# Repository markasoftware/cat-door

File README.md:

# cat-door

KiCAD files and ATtiny84 firmware for my [cat door](https://markasoftware.com/cat-door).

The state machine diagram is old and incorrect. The unit tests in `test.lisp` do
not work, partially because they are written rong, and partially because simavr
seems to have bugs related to inputs with pull-up resistors.

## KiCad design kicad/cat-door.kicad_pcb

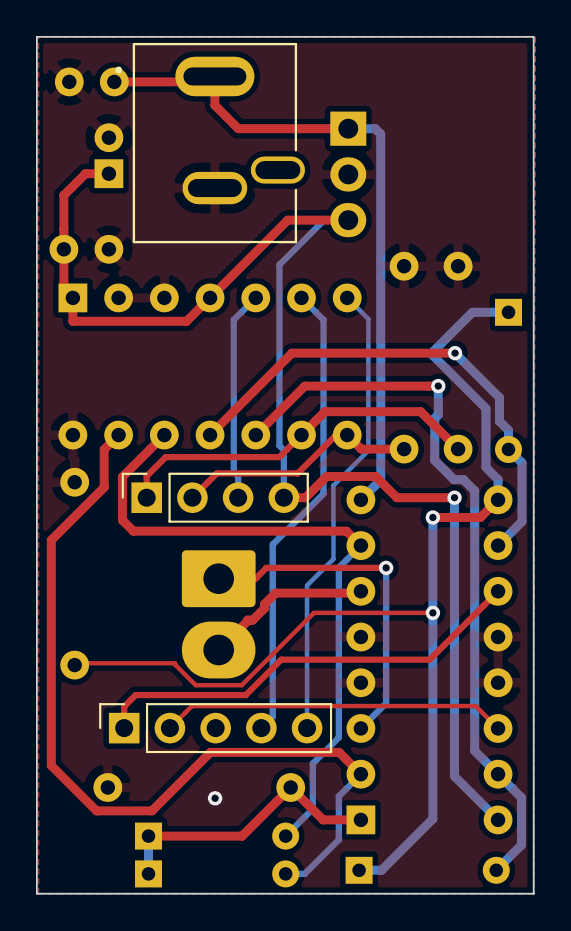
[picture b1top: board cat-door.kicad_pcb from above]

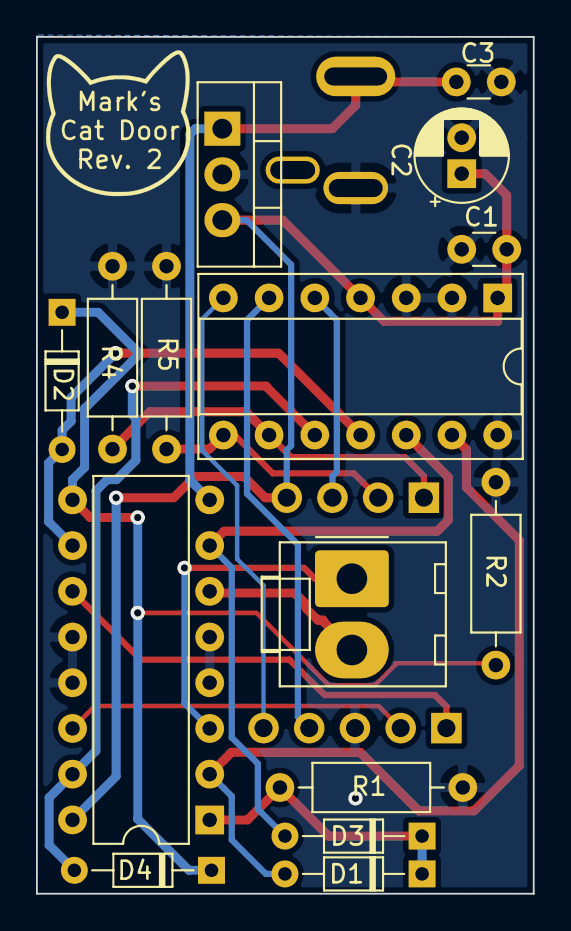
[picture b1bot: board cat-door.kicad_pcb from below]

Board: 2 copper layers, 27.6 x 47.6 mm, 18 parts (15 on the bottom side), 18 nets.

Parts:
C1, C3: .1uF; C_Disc_D3.0mm_W1.6mm_P2.50mm
C2: 10uF; CP_Radial_D5.0mm_P2.00mm
D1, D2, D3, D4: D; D_DO-34_SOD68_P7.62mm_Horizontal
J1: Barrel_Jack_Switch; CUI_PJ-044AH
JCTRL1: Conn_01x04; PinSocket_1x04_P2.54mm_Vertical
JOUTER1: Conn_01x05; PinSocket_1x05_P2.54mm_Vertical
JPENCIL1: Conn_01x02; Molex_KK-396_A-41791-0002_1x02_P3.96mm_Vertical
R1, R2: 22k; R_Axial_DIN0207_L6.3mm_D2.5mm_P10.16mm_Horizontal
R4, R5: 10k; R_Axial_DIN0207_L6.3mm_D2.5mm_P10.16mm_Horizontal
U1: ATtiny84-20PU; DIP-14_W7.62mm_Socket
U2: L293D; DIP-16_W7.62mm
U3: LF50_TO220; TO-220-3_Vertical

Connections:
+5V: C1.1, C2.1, JCTRL1.4, U1.1, U1.4, U2.16, U3.3
+9V: C3.1, J1.1, U2.8, U3.1
/flshgnd: JCTRL1.3, U1.5
/inner_down_o: D3.2, U1.12, U2.7
/inner_up_o: D1.2, U1.13, U2.2
/outer_down_o: D4.2, U1.10, U2.15
/outer_up_o: D2.2, U1.11, U2.10
/sens_closed_i: JOUTER1.4, U1.6
/sens_open_i: JOUTER1.5, U1.7
/sw_closed_i: JCTRL1.2, R5.1, U1.8
/sw_open_i: JCTRL1.1, R4.1, U1.9
GND: C1.2, C2.2, C3.2, J1.2, JOUTER1.3, R1.2, R2.2, R4.2, R5.2, U1.2, U1.3, U1.14, U2.4, U2.5, U2.12, U2.13, U3.2
unnamed: D1.1, D3.1, R1.1, U2.1
unnamed: D2.1, D4.1, R2.1, U2.9
unnamed: JOUTER1.1, U2.11
unnamed: JOUTER1.2, U2.14
unnamed: JPENCIL1.1, U2.3
unnamed: JPENCIL1.2, U2.6

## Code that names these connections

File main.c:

#define F_CPU 128000L

#include <avr/io.h>
#include <avr/interrupt.h>
#include <avr/sleep.h>
#include <util/delay.h>
#include <stdbool.h>

enum action {
	ACT_IDLE,
	// direction for these two is determined by switch position
	ACT_INNER,
	ACT_OUTER,

	// "close" or "open" is sw position when rewind began
	ACT_REWIND_CLOSE,
	ACT_REWIND_OPEN,

	ACT_COOLDOWN,
};

enum pins {
	PIN_INNER_UP_O,
	PIN_INNER_DOWN_O,
	PIN_OUTER_UP_O,
	PIN_OUTER_DOWN_O,
	PIN_SW_OPEN_I,
	PIN_SW_CLOSED_I,
	PIN_SENS_OPEN_I,
	PIN_SENS_CLOSED_I,
};

struct state {
	unsigned char action : 3;
	unsigned char sw_inner_open : 1;
	unsigned char sw_outer_closed : 1;
	unsigned char sens_open : 1;
	unsigned char sens_closed : 1;
	unsigned char inner_done : 1;
};

volatile struct state state = { 0 };

/////////////////////////////////
// pin related functions

static void pin_idle() {
	PORTA &= ~(
		(1<<PIN_INNER_UP_O) |
		(1<<PIN_INNER_DOWN_O) |
		(1<<PIN_OUTER_UP_O) |
		(1<<PIN_OUTER_DOWN_O));
}

// physically move the outer motor up
static void pin_outer_up() {
	pin_idle();
	PORTA |= (1<<PIN_OUTER_UP_O);
}

static void pin_outer_down() {
	pin_idle();
	PORTA |= (1<<PIN_OUTER_DOWN_O);
}

static void pin_inner_up() {
	pin_idle();
	PORTA |= (1<<PIN_INNER_UP_O);
}

static void pin_inner_down() {
	pin_idle();
	PORTA |= (1<<PIN_INNER_DOWN_O);
}

// update switch and sensor info in state using pin information.
static void read_pins() {
	// avoid races
	unsigned char pina = PINA;

	bool new_sw_inner_open = !!(pina & (1<<PIN_SW_OPEN_I));

	// if inner door changed
	if (new_sw_inner_open != state.sw_inner_open) {
		state.inner_done = false;
	}

	state.sw_inner_open = new_sw_inner_open;
	state.sw_outer_closed = !!(pina & (1<<PIN_SW_CLOSED_I));
	// active low (pulled up)
	state.sens_open = !(pina & (1<<PIN_SENS_OPEN_I));
	state.sens_closed = !(pina & (1<<PIN_SENS_CLOSED_I));
}

///////////////////////////
// random helpers

static bool outer_done_p() {
	return (state.sw_outer_closed && state.sens_closed) ||
		(!state.sw_outer_closed && state.sens_open);
}

static void ensure_flshgnd() {
	TCCR0B = (1<<CS02);
	TCCR0A = (1<<COM0A0);
}

static void clear_flshgnd() {
	// stop the counter
	TCCR0B = 0;
	// the next time flshgnd is enabled, we want it to go black immediately.
	if (PINB & (1<<PINB2)) {
		TCNT0 = 2;
	} else {
		TCNT0 = 0;
	}
	// finally, disconnect the OCR
	TCCR0A = 0;
}

////////////////////////////
// state transitions

static void action_idle() {
	clear_flshgnd();
	state.action = ACT_IDLE;
	pin_idle();
	// four and a bit minutes
	OCR1B = TCNT1 + 0x8000;
}

static void action_inner() {
	ensure_flshgnd();
	state.action = ACT_INNER;
	if (state.sw_inner_open) {
		pin_inner_up();
	} else {
		pin_inner_down();
	}
	// two seconds
	OCR1B = TCNT1 + 0x0100;
}

static void action_outer() {
	ensure_flshgnd();
	state.action = ACT_OUTER;
	if (state.sw_outer_closed) {
		pin_outer_down();
	} else {
		pin_outer_up();
	}
	// eight seconds, then rewind
	OCR1B = TCNT1 + 0x0400;
}

static void auto_action_motion() {
	if (state.inner_done) {
		if (outer_done_p()) {
			action_idle();
		} else {
			action_outer();
		}
	} else {
		action_inner();
	}
}

static void action_rewind_close() {
	ensure_flshgnd();
	state.action = ACT_REWIND_CLOSE;
	// should already be set, but for consistency...
	pin_outer_up();
	OCR1B = TCNT1 + 0x0800;
}

static void action_rewind_open() {
	ensure_flshgnd();
	state.action = ACT_REWIND_OPEN;
	pin_outer_down();
	OCR1B = TCNT1 + 0x0800;
}

static void action_cooldown() {
	ensure_flshgnd();
	state.action = ACT_COOLDOWN;
	pin_idle();
	// about a minute
	OCR1B = TCNT1 + 0x2000;
}

///////////////////////////////
// act and act-timer

// perform action and update state accordingly.
static void act() {
	switch (state.action) {
	case ACT_IDLE:
		auto_action_motion();
		break;
	case ACT_INNER:
		// no interrupting inner motor, let timer handle it.
		break;
	case ACT_OUTER:
		// avoid interruptions, for good measure.
		if (state.sens_open || state.sens_closed) {
			auto_action_motion();
		}
		break;
	case ACT_REWIND_CLOSE:
		if (state.sens_closed) {
			// rewind finished gracefully
			auto_action_motion();
		} else if (state.sens_open) {
			// got stuck on the way down during rewind, so it came
			// back up the other (normal spooling) side. Assume a
			// serious blockage.
			action_cooldown();
		}
		break;
	case ACT_REWIND_OPEN:
		if (state.sens_closed || state.sens_open) {
			// rewind finished OR the door got caught while
			// rewinding (never reached the bottom) and is now open
			// but spooled the wrong direction, which will be
			// corrected when the door is next opened.

			// This could cause a loop of activating the motor in
			// case of a serious blockage.
			auto_action_motion();
		}
		break;
	case ACT_COOLDOWN:
		// do nothing, we're waiting for the timer.
		break;
	}
}

// perform action, knowing that the timer compare just fired
static void act_timer() {
	switch (state.action) {
	case ACT_IDLE:
		// Inner door periodic
		state.inner_done = false;
		auto_action_motion();
		// special override
		clear_flshgnd();
		break;
	case ACT_INNER:
		// it's only done if the direction was not changed while it was
		// in motion.
		if (!!(PORTA & (1<<PIN_INNER_UP_O)) == state.sw_inner_open) {
			state.inner_done = true;
		}
		auto_action_motion();
		break;
	case ACT_OUTER:
		// Start rewind
		if (state.sw_outer_closed) {
			action_rewind_close();
		} else {
			action_rewind_open();
		}
		break;

	case ACT_REWIND_OPEN:
	case ACT_REWIND_CLOSE:
		// rewind took too long
		action_cooldown();
		break;
	case ACT_COOLDOWN:
		// cooldown complete
		auto_action_motion();
		break;
	}
}

/////////////////////////////////
// main and interrupts

int main() {
	// Pull high on the door sensors.
	PORTA = (1<<PIN_SENS_OPEN_I) | (1<<PIN_SENS_CLOSED_I);
	// All port A pins are output. Low defaults are OK: Everything off,
	// light solid on.
	DDRA =
		(1<<PIN_INNER_UP_O) |
		(1<<PIN_INNER_DOWN_O) |
		(1<<PIN_OUTER_UP_O) |
		(1<<PIN_OUTER_DOWN_O);
	DDRB = (1<<PINB2); // flshgnd

	// 8-bit timer compare
	OCR0A = 1;

	// enable pin change interrupts
	PCMSK0 =
		(1<<PIN_SW_OPEN_I) |
		(1<<PIN_SW_CLOSED_I) |
		(1<<PIN_SENS_OPEN_I) |
		(1<<PIN_SENS_CLOSED_I);
	GIMSK = (1<<PCIE0);
	_delay_ms(5);

	// timer 1 runs continuously, used for debouncing and inner door timing.
	TCCR1B = (1<<CS12) | (1<<CS10);
	// just make sure it doesn't fire immediately. The first act() should
	// set it properly (door moves immediately).
	OCR1B = 255;
	TIMSK1 = (1<<OCIE1B);

	read_pins();
	act();

	sei();

	while (true) sleep_mode(); // default sleep is idle, allows timers
	// set_sleep_mode can be used for power down, adc sleep, etc
}

// debouncing -- don't read pins until a few tens of milliseconds after the last
// pin change occurred.
ISR(PCINT0_vect) {
	OCR1A = TCNT1 + 4;
	// enable the interrupt
	TIMSK1 = (1<<OCIE1A) | (1<<OCIE1B);
}

// debouncing timer
ISR(TIM1_COMPA_vect) {
	// disable debounce interrupt
	TIMSK1 = (1<<OCIE1B);
	read_pins();
	act();
}

// longer timers
ISR(TIM1_COMPB_vect) {
	act_timer();
}

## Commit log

2020-03-13 initial, but not
2020-03-18 kicad
2020-03-23 PCB seems done
2020-03-23 state machine diagram
2020-03-23 the measurements on the PCb were all wrong. Until now!
2020-03-25 horizontal and vertical traces separated.
2020-06-03 start tests
2020-07-05 lots of stuff. Time to rewrite after hiking!
2020-07-06 rewrite, not working yet
2020-07-06 things are closer to working, but only barely
2020-07-07 Improve rewind logic.
    + No longer "instantly" detect close rewind if the sensor is open --
    use timeouts only for simplicity.
    + "Cooldown" mode detects some sorts of "serious blockages" and turns
    off everything for about a minute.
    + Removed a TODO comment about the periodic timer being set too far in
    the future: That will not happen because pin changes don't happen
2020-07-07 hopefully final changes: Clear flashground during periodic and better control the changing directions of the doors (wait for them to fully open or close before reversing course
2020-07-08 read me
